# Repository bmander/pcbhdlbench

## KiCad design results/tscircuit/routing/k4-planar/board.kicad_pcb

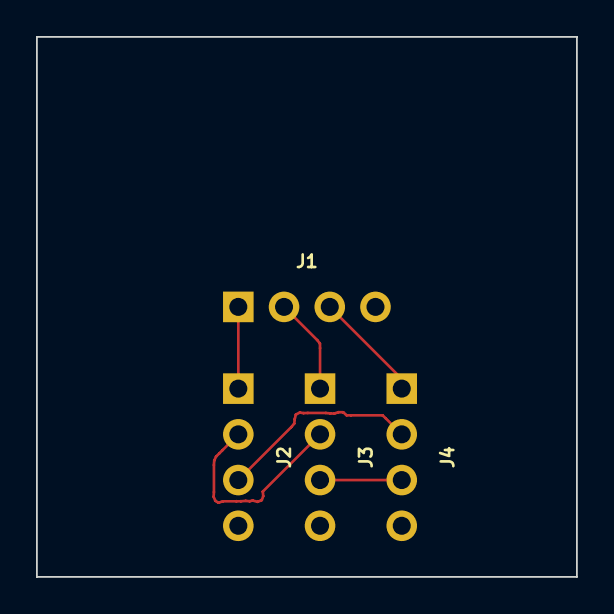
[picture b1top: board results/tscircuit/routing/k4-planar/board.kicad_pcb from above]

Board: 2 copper layers, 30.0 x 30.0 mm, 4 parts (0 on the bottom side), 6 nets.

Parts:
J1: J1; pin_header_pinrow4_p2_54_id1_od1_7_nopinlabels
J2: J2; pin_header_pinrow4_p2_54_id1_od1_7_nopinlabels
J3: J3; pin_header_pinrow4_p2_54_id1_od1_7_nopinlabels
J4: J4; pin_header_pinrow4_p2_54_id1_od1_7_nopinlabels

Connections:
N12: J1.1, J2.1
N13: J1.2, J3.1
N14: J1.3, J4.1
N23: J2.2, J3.2
N24: J2.3, J4.2
N34: J3.3, J4.3

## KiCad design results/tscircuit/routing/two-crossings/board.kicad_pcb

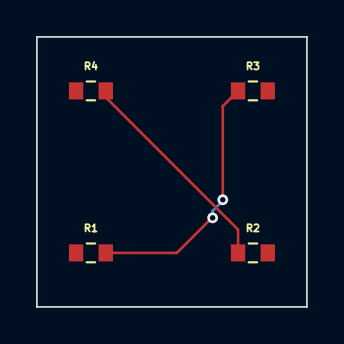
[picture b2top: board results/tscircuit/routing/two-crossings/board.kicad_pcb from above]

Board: 2 copper layers, 15.0 x 15.0 mm, 4 parts (0 on the bottom side), 2 nets.

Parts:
R1, R2, R3, R4: 1kΩ; resistor_res0603

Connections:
.R1 > .pin2 to .R3 > .pin1: R1.2, R3.1
.R2 > .pin1 to .R4 > .pin2: R2.1, R4.2

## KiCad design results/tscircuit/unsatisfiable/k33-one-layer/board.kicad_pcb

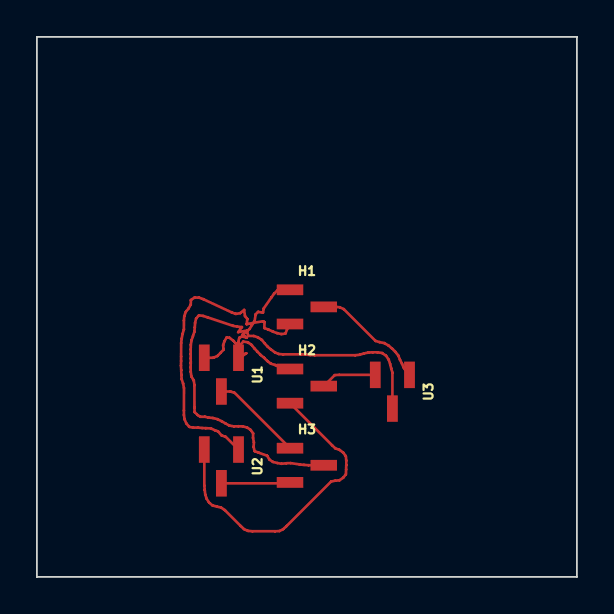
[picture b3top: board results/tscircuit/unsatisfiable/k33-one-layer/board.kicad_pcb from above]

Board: 2 copper layers, 30.0 x 30.0 mm, 6 parts (0 on the bottom side), 9 nets.

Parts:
H1, H2, H3: chip_sot23_w1_875mm_pl1_475mm
U1, U2, U3: chip_sot23_w1_875mm_pl1_475mm

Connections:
.H1 > .pin1 to .U1 > .pin1: H1.1, U1.1
.H1 > .pin2 to .U2 > .pin1: H1.2, U2.1
.H1 > .pin3 to .U3 > .pin1: H1.3, U3.1
.H2 > .pin1 to .U1 > .pin2: H2.1, U1.2
.H2 > .pin2 to .U2 > .pin2: H2.2, U2.2
.H2 > .pin3 to .U3 > .pin2: H2.3, U3.2
.H3 > .pin1 to .U1 > .pin3: H3.1, U1.3
.H3 > .pin2 to .U2 > .pin3: H3.2, U2.3
.H3 > .pin3 to .U3 > .pin3: H3.3, U3.3

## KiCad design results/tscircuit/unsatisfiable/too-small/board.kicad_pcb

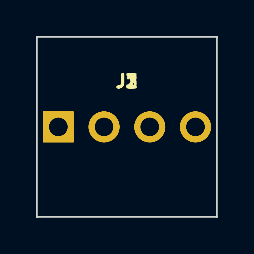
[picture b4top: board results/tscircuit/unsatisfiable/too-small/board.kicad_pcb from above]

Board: 2 copper layers, 10.0 x 10.0 mm, 3 parts (0 on the bottom side), 4 nets, no tracks yet.

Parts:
J1: J1; pin_header_pinrow4_p2_54_id1_od1_7_nopinlabels
J2: J2; pin_header_pinrow4_p2_54_id1_od1_7_nopinlabels
J3: J3; pin_header_pinrow4_p2_54_id1_od1_7_nopinlabels

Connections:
N1: J1.1, J2.1, J3.1
N2: J1.2, J2.2, J3.2
N3: J1.3, J2.3, J3.3
N4: J1.4, J2.4, J3.4
